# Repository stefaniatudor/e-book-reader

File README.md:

## Functionalitate Hardware

ESP32-C6 este procesorul principal si se ocupa de comunicatie si control. Are Wi-Fi 6 si Bluetooth Low Energy integrate. Toate componentele externe sunt conectate prin magistrale digitale standard pentru a fi usor de extins sau modificat.

- **E-paper Display (SPI):** Ecran cu consum foarte mic, ideal pentru afisarea textului static. Nu consuma curent intre actualizari.
- **BME680 (I2C):** Senzor care masoara temperatura, umiditate, presiune si calitatea aerului.
- **DS3231SN (I2C):** Ceas in timp real (RTC) cu baterie de rezerva. Pastreaza ora corecta chiar si cand dispozitivul este oprit.
- **W25Q512JVEIQ (SPI):** Memorie externa de 64MB pentru stocarea cartilor si a setarilor. Viteza mare de scriere/citire.
- **MAX17048 (I2C):** Monitor de baterie care estimeaza nivelul de incarcare in timp real.
- **Conector QWIIC + Header GPIO:** Permite conectarea de module suplimentare, cum ar fi senzori, ecrane, etc.

## Alimentare si Management Energie

- **Baterie principala:** 3.7V Li-Po, folosita pentru alimentarea intregului dispozitiv.
- **Convertor de tensiune (LDO):** Combinatie intre DMG2305UX (MOSFET pentru control) si XC6220A331MR-G (LDO) – converteste tensiunea bateriei la 3.3V cu un curent maxim de 300 mA.
- **Incarcare baterie:** Se face prin USB-C, folosind circuitul dedicat MCP73831, un incarcator liniar pentru baterii Li-Po.
- **Monitorizare baterie:** Circuitul MAX17048 estimeaza cu precizie nivelul de incarcare al bateriei si trimite informatia catre ESP32-C6 prin I2C.
- **Protectie la descarcari electrostatice (ESD):**
  - La intrarea USB-C este folosit un varistor si o dioda USBLC6-2SC6Y pentru protectie.
  - Liniile SPI (folosite pentru ecran si memorie flash) sunt protejate cu componente dedicate ESD, pentru siguranta la conectarea externa sau descarcari accidentale.

## Conexiuni ESP32-C6

| Functionalitate      | Pin ESP32-C6                          | Descriere                                                                 |
|----------------------|----------------------------------------|---------------------------------------------------------------------------|
| UART pentru debug    | TX / RX                                | Conectat la USB-C pentru programare si comunicatie seriala cu PC-ul      |
| I2C                  | IO4 (SCL), IO5 (SDA)                   | Folosit pentru BME680, DS3231 si conectorul Qwiic                        |
| SPI                  | IO10 (CLK), IO11 (MOSI), IO12 (MISO), IO13 (CS) | Comunica cu memoria flash si ecranul e-paper                      |
| Buton BOOT           | IO9                                    | Buton conectat la linia de BOOT pentru programare                        |
| LED Status           | IO6                                    | LED utilizat pentru semnalizare vizuala (pornit, incarcare, standby etc.)|
| GPIO-uri libere      | IO0, IO1, IO2, IO3                      | Disponibile pentru extensii viitoare                                     |

## Bill of Materials (BOM)

- **BME680**  
  - Link: https://www.snapeda.com/parts/BME680/Bosch/view-part/?welcome=home  
  - Datasheet: https://www.snapeda.com/parts/BME680/Bosch%20Sensortec/datasheet/

- **DMG2305UX-7**  
  - Link: https://componentsearchengine.com/part-view/DMG2305UX-7/Diodes%20Incorporated  
  - Datasheet: https://www.diodes.com//assets/Datasheets/DMG2305UX.pdf

- **W25Q512JVEIQ**  
  - Link: https://www.snapeda.com/parts/W25Q512JVEIQ/Winbond+Electronics/view-part/?ref=eda  
  - Datasheet: https://www.snapeda.com/parts/W25Q512JVEIQ/Winbond%20Electronics/datasheet/

- **MAX17048G+T10**  
  - Link: https://www.snapeda.com/parts/MAX17048G+T10/Analog+Devices/view-part/?ref=eda  
  - Datasheet: https://www.snapeda.com/parts/MAX17048G+T10/Analog%20Devices/datasheet/

- **DS3231SN**  
  - Link: https://www.snapeda.com/parts/DS3231SN%23/Analog+Devices/view-part/?ref=eda  
  - Datasheet: https://www.snapeda.com/parts/DS3231SN%23/Analog%20Devices/datasheet/

- **MCP73831**  
  - Link: https://www.digikey.com/en/models/1874108  
  - Datasheet: —

- **XC6220A331MR-G**  
  - Link: https://componentsearchengine.com/part-view/XC6220A331MR-G/Torex  
  - Datasheet: https://product.torexsemi.com/system/files/series/xc6220.pdf

- **USBLC6-2SC6Y**  
  - Link: https://www.snapeda.com/parts/USBLC6-2SC6Y/STMicroelectronics/view-part/?ref=eda  
  - Datasheet: https://www.snapeda.com/parts/USBLC6-2SC6Y/STMicroelectronics/datasheet/

- **QWIIC PRT-14417**  
  - Link: https://www.snapeda.com/parts/PRT-14417/SparkFun/view-part/  
  - Datasheet: https://www.snapeda.com/parts/PRT-14417/SparkFun%20Electronics/datasheet/

- **ESP32-C6-WROOM-1-N8**  
  - Link: https://www.snapeda.com/parts/ESP32-C6-WROOM-1-N8/Espressif+Systems/view-part/?ref=eda  
  - Datasheet: https://www.snapeda.com/parts/ESP32-C6-WROOM-1-N8/Espressif%20Systems/datasheet/

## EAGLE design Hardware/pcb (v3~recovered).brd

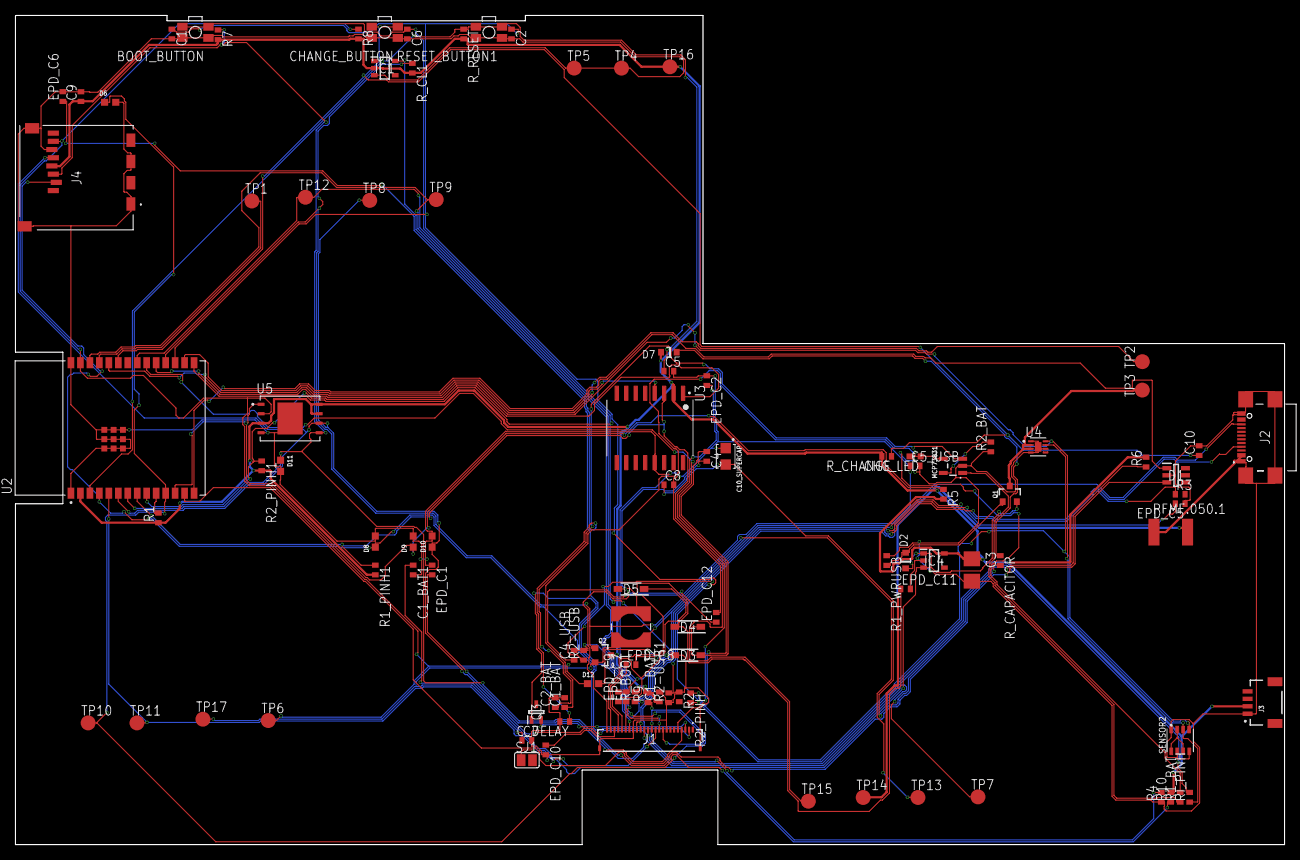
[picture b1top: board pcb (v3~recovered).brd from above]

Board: 2 copper layers, 170.2 x 111.2 mm, 103 parts (0 on the bottom side), 57 nets.

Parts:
BOOT_BUTTON: MYBUTTON
C1, C2, C6, C8, C10: 100nF; ESP32_WROVER_EAGLE-LTSPICE_C0402
C1_BAT, C1_BAT2, C2_BAT: 4.7uF; ESP32_WROVER_EAGLE-LTSPICE_C0402
C1_BAT1, C5_USB: 4.7uF; EAGLE-LTSPICE_C0402
C3: 100uF TANT; RCL_CT3528
C4: 4.7uF/25V; ESP32_WROVER_EAGLE-LTSPICE_C0402
C4_USB, C9: 100nF; EAGLE-LTSPICE_C0402
C5: 1uF; ESP32_WROVER_EAGLE-LTSPICE_C0402
C7: 10uF; ESP32_WROVER_EAGLE-LTSPICE_C0402
C10_SUPERCAP: CPH3225A; CAPCP3225X100N
CHANGE_BUTTON: MYBUTTON
CHG_LED: ADAFRUIT_CHIP-LED0603
C_DELAY: 100nF; ESP32_WROVER_EAGLE-LTSPICE_C0402
D1: USBLC6-2SC6Y; SOT95P280X145-6N
D2, D7: ESP32_WROVER_AVX---SD0805S020S1R0_AVX_SD0805S020S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; ESP32_WROVER_AVX---SD0805S020S1R0_AVX_SD0805S020S1R0_0
D3, D4, D5: MBR0530; SOD3716X135N
D6, D8, D9, D10, D11, D12: PGB1010603MR; DIOC1608X36N
EPD_C1, EPD_C2, EPD_C6, EPD_C7, EPD_C8, EPD_C9, EPD_C11, EPD_C12: 1uF/50V; ESP32_WROVER_EAGLE-LTSPICE_C0402
EPD_C5: 01uf/50V; ESP32_WROVER_EAGLE-LTSPICE_C0402
EPD_C10: 1uf/50V; ESP32_WROVER_EAGLE-LTSPICE_C0402
IC1: BD5229G-TR; SOT95P280X120-5N
IC4: XC6220A331MR-G; SOT95P280X120-5N
J1: FH34SRJ-24S-0.5SH_99_; FH34SRJ24S05SH99
J2: SAMACSYS_PARTS_USB4110-GF-A; SAMACSYS_PARTS_USB4110GFA
J3: QWIIC_RIGHT_ANGLE; JST04_1MM_RA
J4: 112A-TAAR-R03_ATTEND; 112ATAARR03ATTEND
L1: 68uH; IND_4828-WE-TPC_WRE
MCP73831: ESP32_WROVER_SPARKFUN-IC-POWER_MCP73831; ESP32_WROVER_SPARKFUN-IC-POWER_SOT23-5
PFMF.050.1: ESP32C6_VARISTORCN1812; ESP32C6_VARISTOR_CT/CN1812
Q1, Q2: 20V/4.2A/52mΩ/1.4W; ESP32_WROVER_SPARKFUN-DISCRETESEMI_SOT23-3
Q3: SI1308EDL-T1-GE3; SOT65P210X110-3N
R1: 10k; ESP32_WROVER_EAGLE-LTSPICE_R0402
R1_BAT: 200; ESP32_WROVER_EAGLE-LTSPICE_R0402
R1_PINH1, R2_PINH, R2_PINH1, R4, R5, R6, R7, R8, R9, R10: 10K; ESP32_WROVER_EAGLE-LTSPICE_R0402
R1_PWRUSB: 100k; ESP32_WROVER_EAGLE-LTSPICE_R0402
R2: 2.2; ESP32_WROVER_EAGLE-LTSPICE_R0402
R2-USB, R2-USB1: 5k1; ESP32_WROVER_EAGLE-LTSPICE_R0402
R2_BAT: 2k; ESP32_WROVER_EAGLE-LTSPICE_R0402
R3: 0.47; ESP32_WROVER_EAGLE-LTSPICE_R0402
RESET_BUTTON1: MYBUTTON
RI_PINH: 10K; ESP32_WROVER_EAGLE-LTSPICE_R0402
R_BOOT: 10K; ESP32_WROVER_EAGLE-LTSPICE_R0402
R_CAPACITOR: 15; ESP32_WROVER_EAGLE-LTSPICE_R0402
R_CHANGE: 10K; ESP32_WROVER_EAGLE-LTSPICE_R0402
R_CL1: 10K; ESP32_WROVER_EAGLE-LTSPICE_R0402
R_RESET: 10K; ESP32_WROVER_EAGLE-LTSPICE_R0402
SENSOR2: BME688; ESP32_WROVER_BME680_PSON80P300X300X100-8N
SJ1: SJ
TP1, TP2, TP3, TP4, TP5, TP6, TP7, TP8, TP9, TP10, TP11, TP12, TP13, TP14, TP15, TP16, TP17: TPTP20R; TP20R
U2: ESP32-C6-WROOM-1-N8; XCVR_ESP32-C6-WROOM-1-N8
U3: DS3231SN#; SOIC127P1032X265-16N
U4: MAX17048G+T10; SON50P200X200X80-9N
U5: W25Q512JVEIQ; SON127P600X800X80-9N

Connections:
3V3: C1_BAT2.1, C3.+, C9.1, D7.2, IC1.2, IC4.5, J3.2, J4.P4, Q2.3, R1.1, R1_PINH1.2, R2_PINH1.2, R5.2, R6.2, R7.2, R8.2, R9.2, R10.2, R_BOOT.2, R_CHANGE.2, R_CL1.2, R_RESET.2, TP16.TP, U2.2, U3.2, U5.3, U5.7, U5.8
32KHZ: R2_PINH1.1, U2.9, U3.1
EPD_3V3: C7.1, EPD_C5.2, J1.15, J1.16, L1.2, Q2.2, TP17.TP
EPD_3V3_C: Q2.1, R_CL1.1, TP13.TP, U2.18
EPD_BUSY: J1.9, TP9.TP, U2.26
EPD_CS: D6.1, J1.12, R9.1, TP10.TP, U2.11
EPD_DC: J1.11, TP11.TP, U2.5
EPD_RST: J1.10, TP12.TP, U2.21
FLASH_CS: D9.1, R5.1, U2.12, U5.1
GDR: J1.2, Q3.1, R4.2
GND: BOOT_BUTTON.1, BOOT_BUTTON.2, C1.2, C1_BAT.2, C1_BAT1.2, C1_BAT2.2, C2.2, C2_BAT.2, C3.-, C4_USB.2, C5.2, C5_USB.2, C6.2, C7.2, C8.2, C9.2, C10.2, C10_SUPERCAP.1, CHANGE_BUTTON.1, CHANGE_BUTTON.2, C_DELAY.2, D1.2, D3.1, D6.2, D8.2, D9.2, D10.2, D11.2, D12.2, EPD_C1.1, EPD_C2.1, EPD_C5.1, EPD_C6.2, EPD_C7.2, EPD_C8.2, EPD_C9.2, EPD_C10.2, EPD_C11.2, EPD_C12.2, IC1.3, IC4.2, J1.8, J1.17, J1.MP1, J1.MP2, J2.A1, J2.A12, J2.B1, J2.B12, J2.MP1, J2.MP2, J2.MP3, J2.MP4, J3.1, J4.G1, J4.G2, J4.G3, J4.G4, J4.P6, MCP73831.2, R1_PWRUSB.1, R2.1, R2-USB.2, R2-USB1.1, R2_BAT.1, R4.1, RESET_BUTTON1.1, RESET_BUTTON1.2, SENSOR2.1, SENSOR2.5, SENSOR2.7, SJ1.1, TP4.TP, TP5.TP, U2.1, U2.28, U2.29_1, U2.29_2, U2.29_3, U2.29_4, U2.29_5, U2.29_6, U2.29_7, U2.29_8, U2.29_9, U3.13, U4.1, U4.4, U4.6, U4.9, U5.4, U5.9
GPIO8: R1.2, U2.10
I2C_PW: C1.1, C2.1, R2_PINH.2, RI_PINH.2, U2.17
IC2_PW: SENSOR2.2, SENSOR2.6, SENSOR2.8
INT_RTC: R1_PINH1.1, TP15.TP, U2.8, U3.3
IO/BOOT: BOOT_BUTTON.3, BOOT_BUTTON.4, C6.1, R_BOOT.1, U2.15
IO/CHANGE: C10.1, CHANGE_BUTTON.3, CHANGE_BUTTON.4, R_CHANGE.1, U2.23
MISO: D12.1, J4.P7, R8.1, TP6.TP, U2.27, U5.2
MOSI: D11.1, J1.14, J4.P3, R7.1, TP7.TP, U2.7, U5.5
unnamed: J2.B5, R2-USB.1
unnamed: J2.A5, R2-USB1.2
unnamed: C4_USB.1, C5_USB.1
unnamed: D2.2, Q1.1, R1_PWRUSB.2
unnamed: C1_BAT1.1, D2.1, IC4.1, IC4.3, Q1.2
unnamed: MCP73831.1, R1_BAT.1
unnamed: C4.2, D5.2, L1.1
unnamed: C4.1, D3.2, D4.1
unnamed: CHG_LED.C, R1_BAT.2
unnamed: C1_BAT.1, CHG_LED.A, MCP73831.4
unnamed: MCP73831.5, R2_BAT.2
unnamed: EPD_C1.2, J1.4
unnamed: EPD_C2.2, J1.5
unnamed: EPD_C6.1, J1.18
unnamed: EPD_C7.1, J1.19
unnamed: EPD_C8.1, J1.20
unnamed: EPD_C10.1, J1.22
unnamed: EPD_C12.1, J1.24
unnamed: C_DELAY.1, IC1.5
unnamed: D7.1, R_CAPACITOR.1
PREVGH: D5.1, EPD_C9.1, J1.21
PREVGL: D4.2, EPD_C11.1, J1.23
RESE: J1.3, Q3.2, R3.1
RESET: C5.1, IC1.1, RESET_BUTTON1.3, RESET_BUTTON1.4, R_RESET.1, U2.3
RTC_RST: U2.16, U3.4
RX: TP2.TP, U2.24
SCK: D10.1, J1.13, J4.P5, R6.1, TP8.TP, U2.6, U5.6
SCL: R2_PINH.1, SENSOR2.4, U2.20, U4.7
SDA: RI_PINH.1, SENSOR2.3, U2.19, U4.8
SS_SD: D8.1, J4.P2, R10.1, U2.4
TX: TP1.TP, U2.25
USB_D+: D1.1, U2.14
USB_D-: D1.3, U2.13
VBAT: Q1.3, TP3.TP, U4.2, U4.3
VBBAT: C2_BAT.1, MCP73831.3
VBUS: PFMF.050.1.2, TP14.TP
VRTC: C8.1, C10_SUPERCAP.2, R_CAPACITOR.2
VUSB: J2.A4, PFMF.050.1.1

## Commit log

2025-04-06 Create s
2025-04-06 Create LICENSE

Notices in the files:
parts and their libraries:
COPYRIGHT: Copyright (C) 2024 Ultra Librarian. All rights reserved.
